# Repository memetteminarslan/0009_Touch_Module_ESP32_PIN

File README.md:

# 0009_Touch_Module_ESP32_PIN

You are seeing a large number of widely used Touch modules in electronic development kits. More information coming soon...

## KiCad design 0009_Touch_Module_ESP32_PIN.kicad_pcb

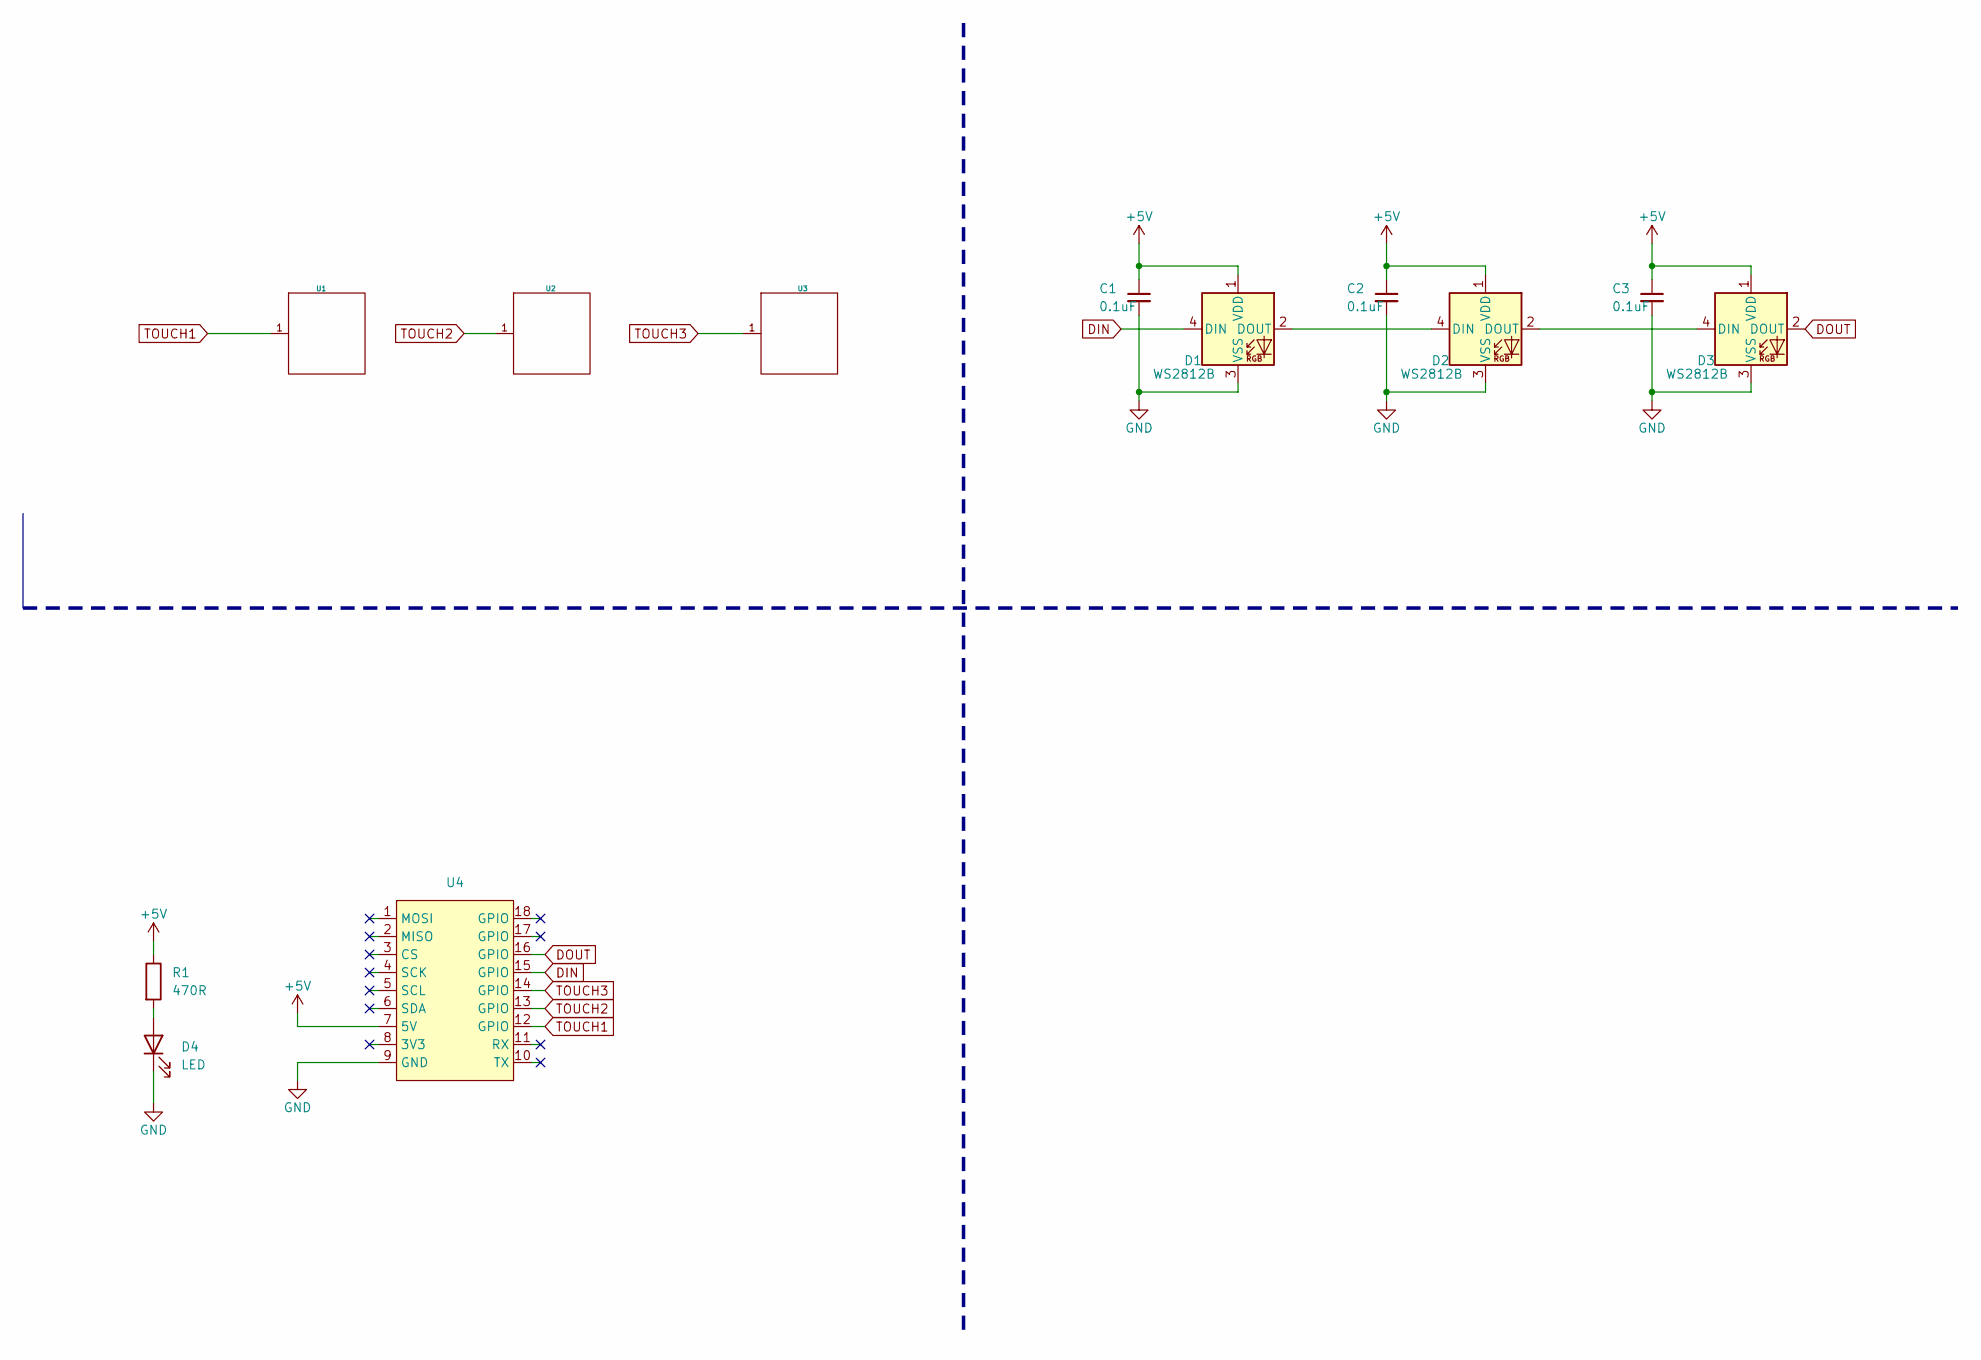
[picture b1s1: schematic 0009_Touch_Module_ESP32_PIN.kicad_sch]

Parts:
C1, C2, C3: 0.1uF; C_0603_1608Metric
D1, D2, D3: WS2812B; LED_WS2812B_PLCC4_5.0x5.0mm_P3.2mm
D4: LED; LED_0603_1608Metric
R1: 470R; R_0603_1608Metric
U1, U2, U3: touch
U4: air_module

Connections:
+5V: C1.1, C2.1, C3.1, D1.1 (VDD), D2.1 (VDD), D3.1 (VDD), R1.1, U4.7 (5V)
DIN: D1.4 (DIN), U4.15 (GPIO)
DOUT: D3.2 (DOUT), U4.16 (GPIO)
GND: C1.2, C2.2, C3.2, D1.3 (VSS), D2.3 (VSS), D3.3 (VSS), D4.1 (K), U4.9 (GND)
unnamed: D1.2 (DOUT), D2.4 (DIN)
unnamed: D2.2 (DOUT), D3.4 (DIN)
unnamed: D4.2 (A), R1.2
TOUCH1: U1.1, U4.12 (GPIO)
TOUCH2: U2.1, U4.13 (GPIO)
TOUCH3: U3.1, U4.14 (GPIO)

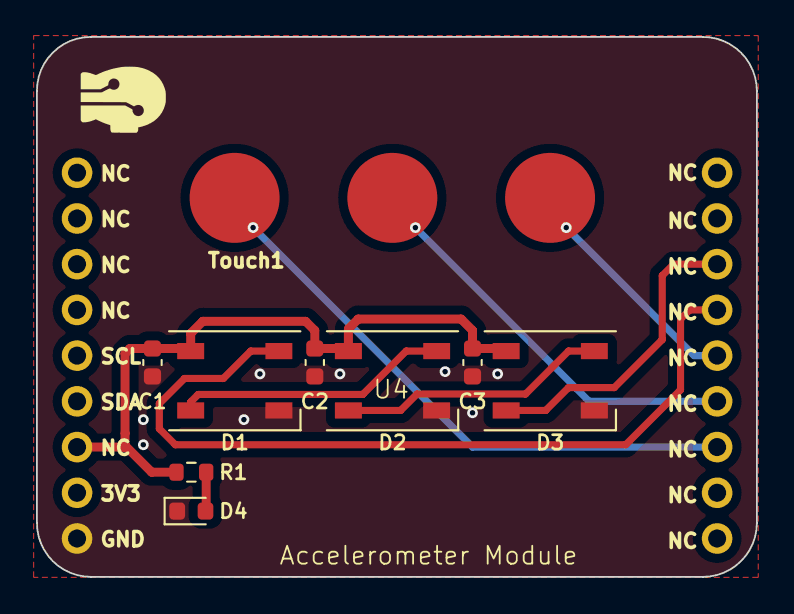
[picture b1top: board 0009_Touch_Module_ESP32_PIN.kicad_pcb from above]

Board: 2 copper layers, 40.0 x 30.0 mm, 12 parts (0 on the bottom side), 10 nets.
